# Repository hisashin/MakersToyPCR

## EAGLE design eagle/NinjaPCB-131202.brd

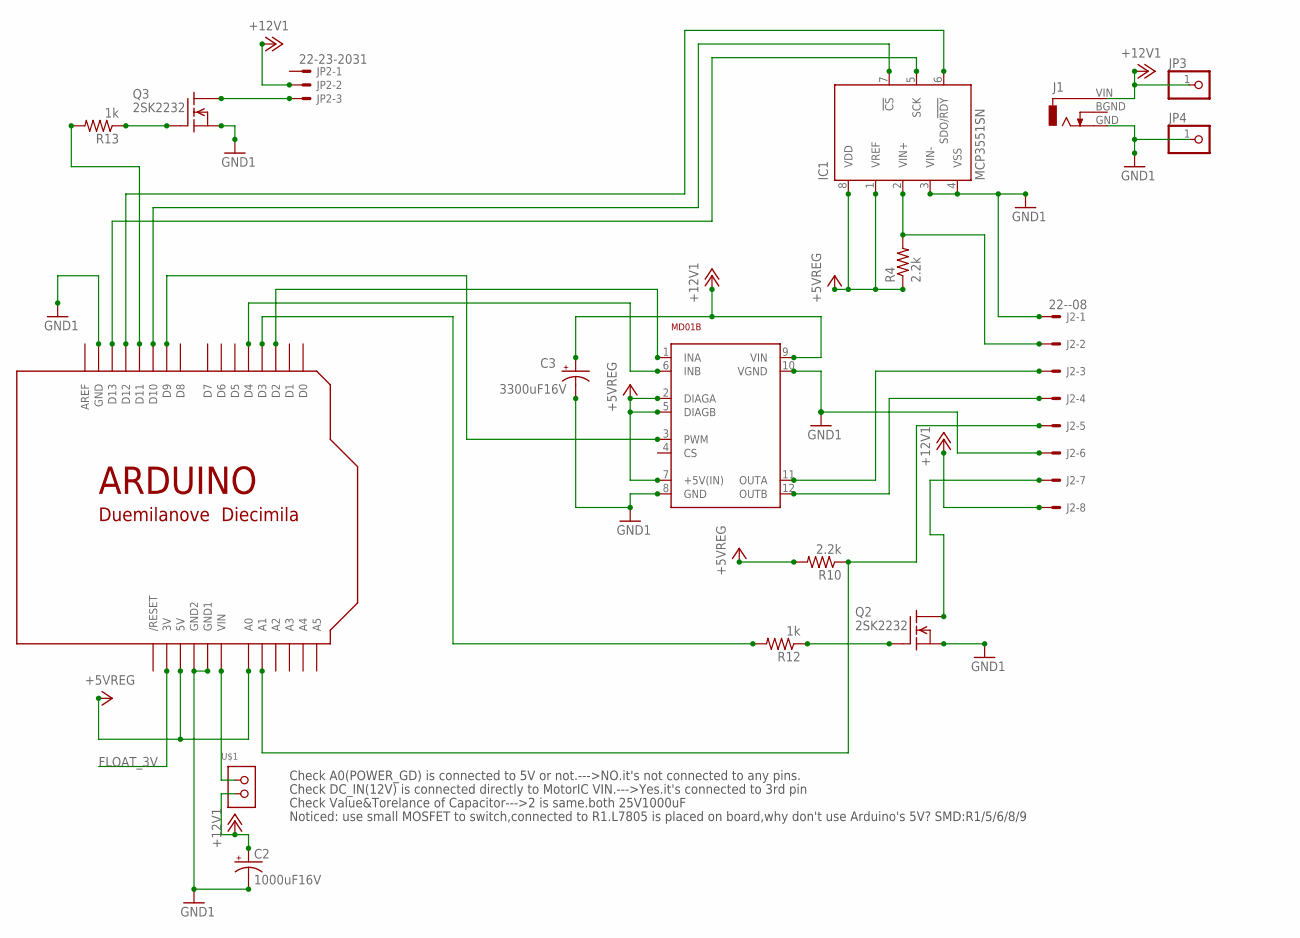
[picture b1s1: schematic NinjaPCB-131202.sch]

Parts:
C2: 1000uF16V; E5-8,5
C3: 3300uF16V; E5-13
IC1: MCP3551SN; SO-08
J1: DCJ0303
J2: 22--08; POLOLU-8-VERTICAL
JP2: 22-23-2031
JP3, JP4: PINHD-1X1; 1X01
MD01B: VNH3SP30+4PINN; VNH3SP30+4PIN_NOHOLES
Q2, Q3: 2SK2232; TO202
R4, R10: 2.2k; 0207/10
R12, R13: 1k; 0207/10
U$1: 1X02; 1X02_1.1_UNSIGNED
U$3: Arduino UNO; ARDUINO-NOSILK

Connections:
+5VREG: IC1.1 (VREF), IC1.8 (VDD), MD01B.2 (DIAGA), MD01B.5 (DIAGB), MD01B.7 (+5V(IN)), R4.1, R10.2, U$3.5V, U$3.A0
+12V1: C2.+, C3.+, J1.VIN, J2.8, JP2.2, JP3.1, MD01B.9 (VIN), U$1.2
D13: IC1.5 (SCK), U$3.D13
FLOAT_3V: U$3.3V
GND1: C2.-, C3.-, IC1.3 (VIN-), IC1.4 (VSS), J1.GND, J2.1, J2.6, JP4.1, MD01B.8 (GND), MD01B.10 (VGND), Q2.1 (S), Q3.1 (S), U$3.GND, U$3.GND1, U$3.GND2
unnamed: JP2.3, Q3.2 (D)
unnamed: Q3.3 (G), R13.1
unnamed: R13.2, U$3.D11
unnamed: U$1.1, U$3.VIN
unnamed: R12.2, U$3.D3
unnamed: J2.7, Q2.2 (D)
unnamed: IC1.2 (VIN+), J2.2, R4.2
unnamed: IC1.6 (SDO/!RDY), U$3.D12
unnamed: IC1.7 (!CS), U$3.D10
unnamed: J2.5, R10.1, U$3.A1
OUTA: J2.3, MD01B.11 (OUTA)
OUTB: J2.4, MD01B.12 (OUTB)
S$1: MD01B.1 (INA), U$3.D2
S$2: MD01B.3 (PWM), U$3.D9
S$3: MD01B.6 (INB), U$3.D4
T1: Q2.3 (G), R12.1

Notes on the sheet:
Check A0(POWER_GD) is connected to 5V or not.--->NO.it's not connected to any pins.
Check DC_IN(12V) is connected directly to MotorIC VIN.--->Yes.it's connected to 3rd pin
Check Value&Torelance of Capacitor--->2 is same.both 25V1000uF
Noticed: use small MOSFET to switch,connected to R1.L7805 is placed on board,why don't use Arduino's 5V? SMD:R1/5/6/8/9

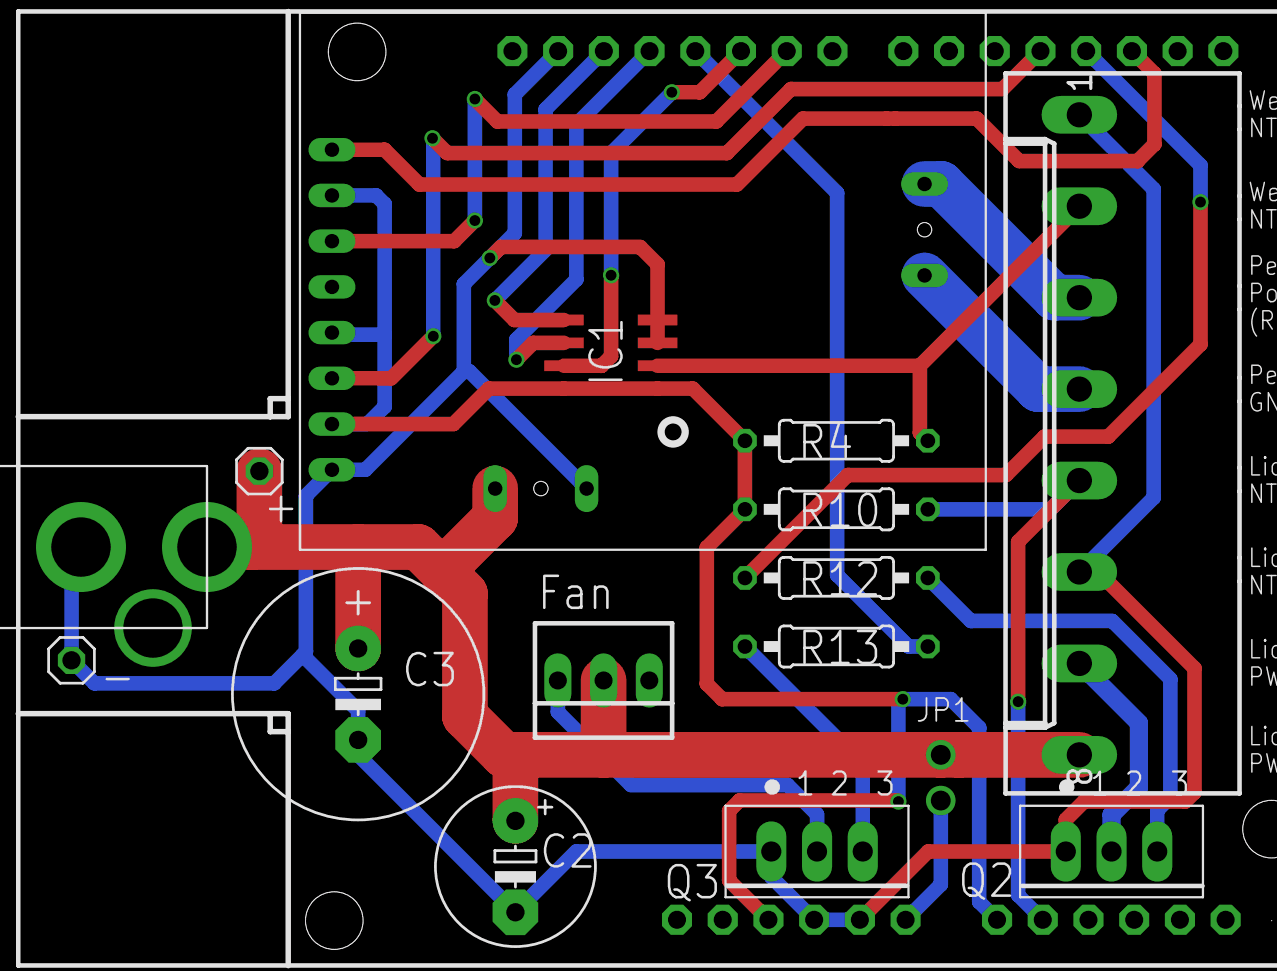
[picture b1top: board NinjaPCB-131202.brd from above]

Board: 2 copper layers, 17 parts (0 on the bottom side), 20 nets.

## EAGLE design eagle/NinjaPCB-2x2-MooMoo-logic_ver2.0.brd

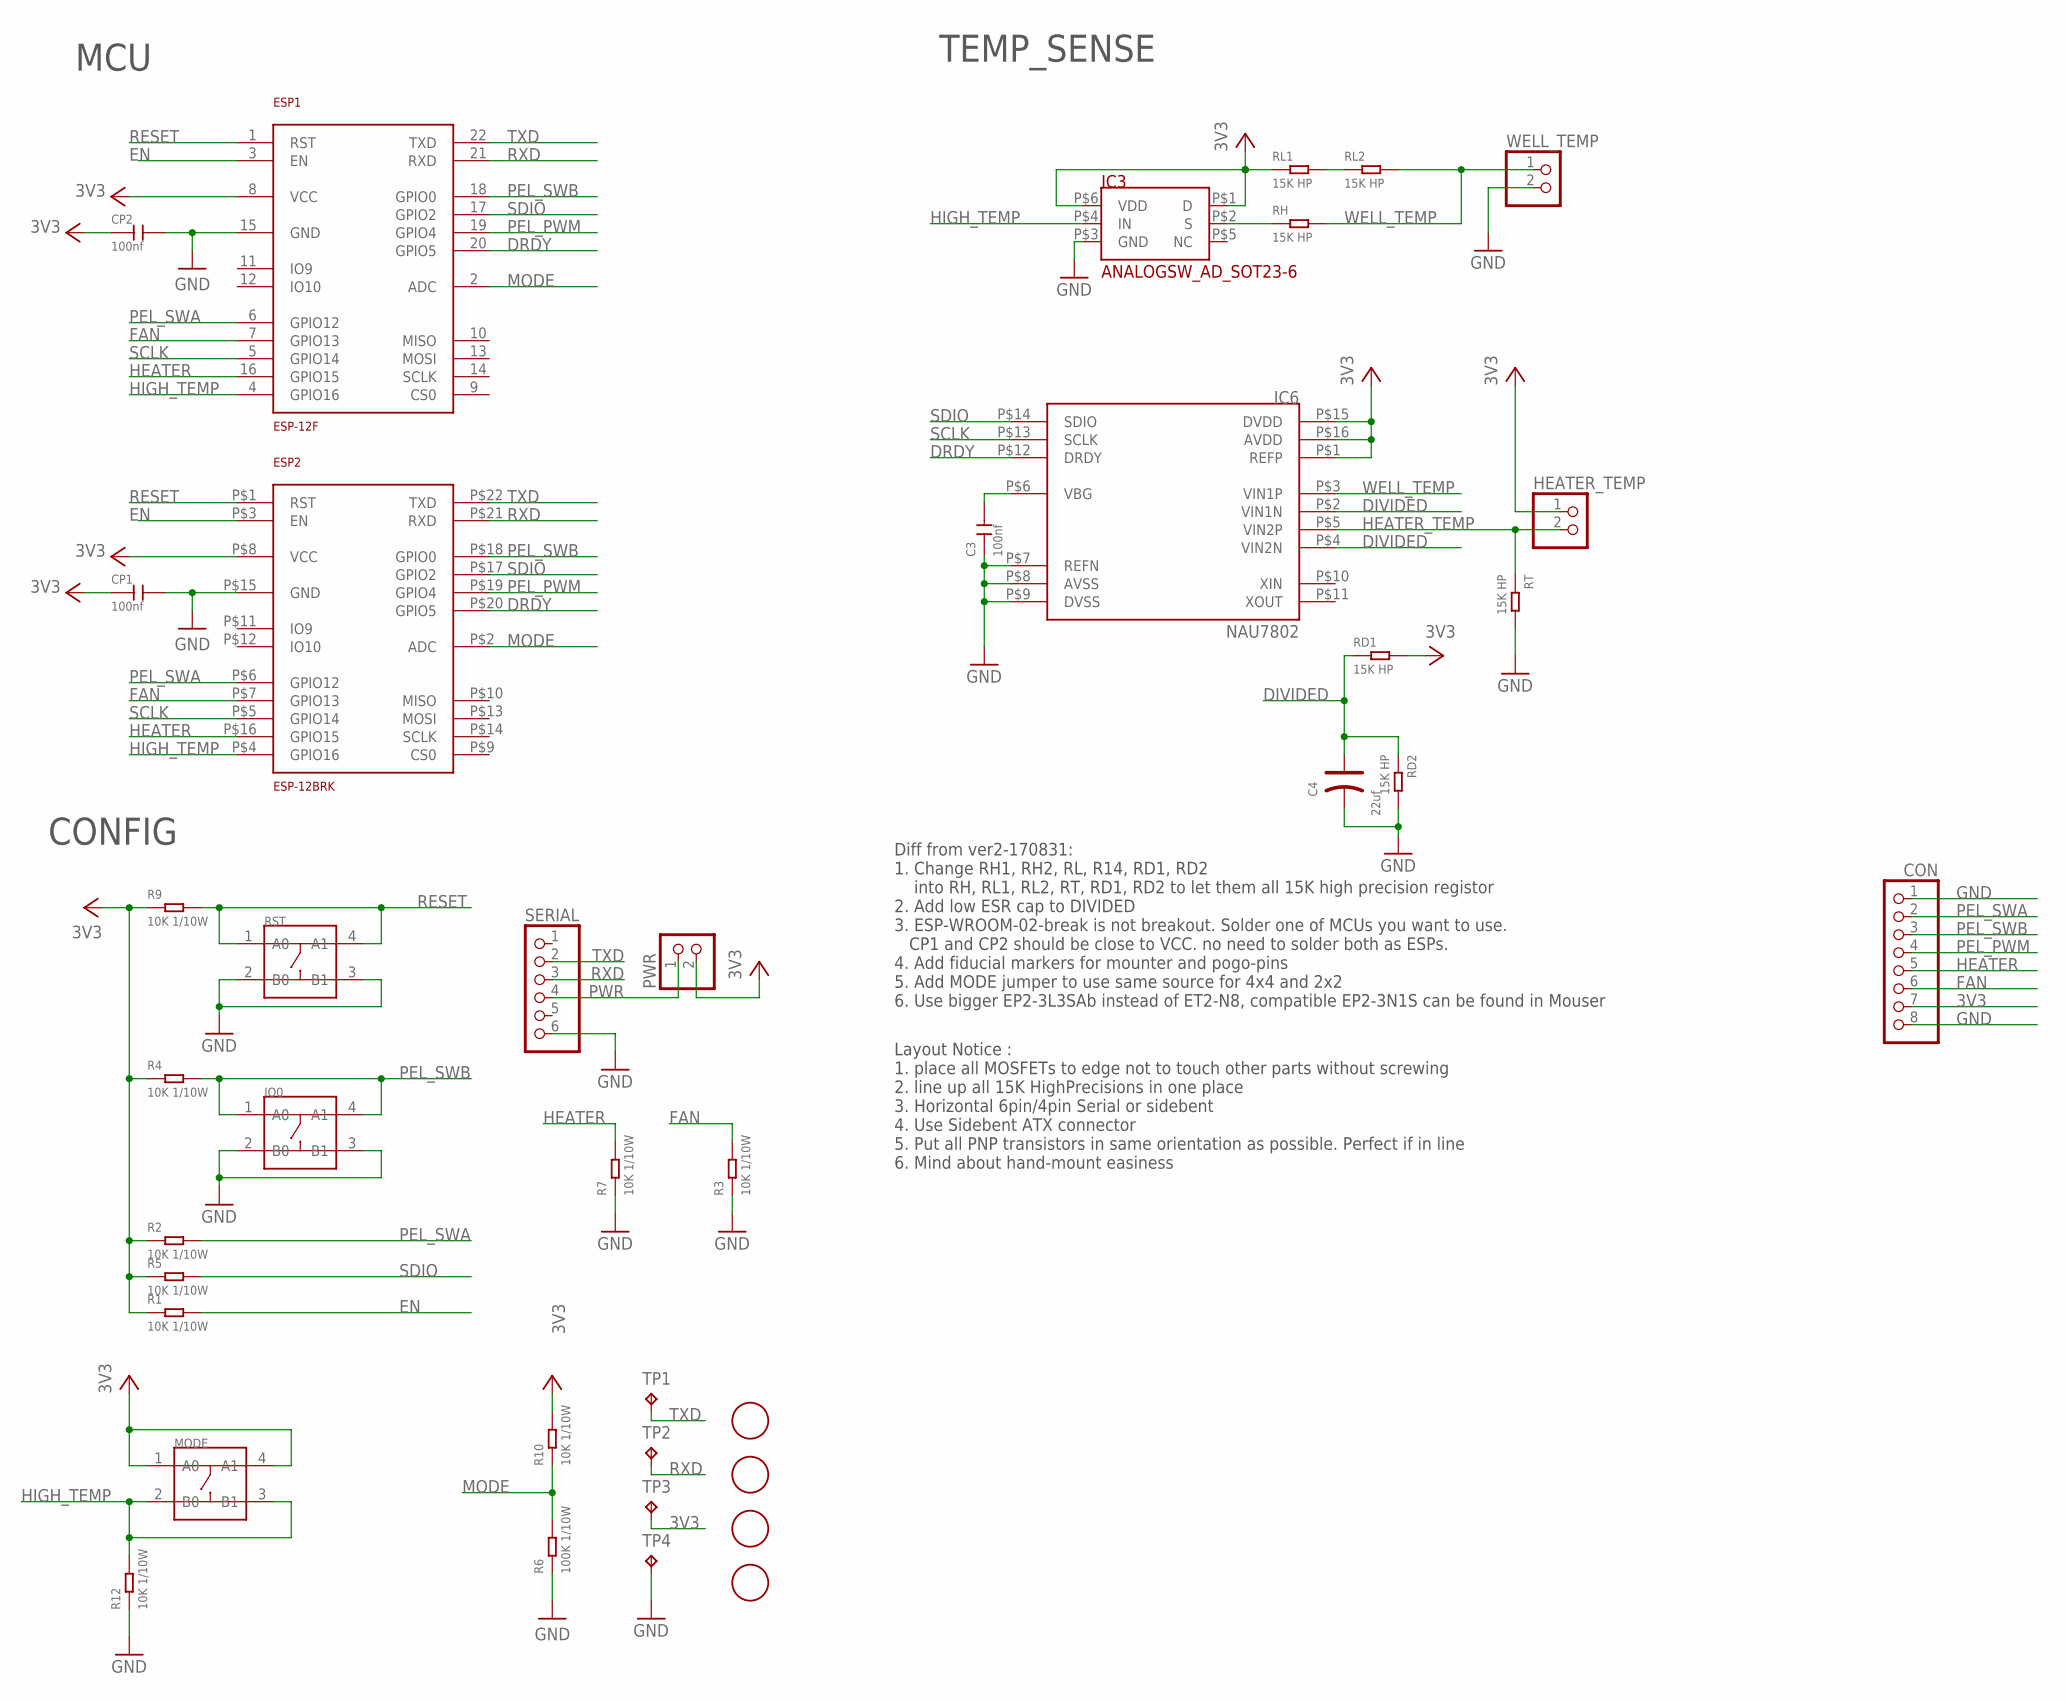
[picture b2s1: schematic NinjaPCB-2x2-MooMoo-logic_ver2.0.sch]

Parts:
C3: 100nf; C0603
C4: 22uf; AVX-B
CON: PINHD-1X8; 1X08
CP1, CP2: 100nf; C0603
ESP1: ESP-12F
ESP2: ESP-12BRK; ESP-12-BREAK
HEATER_TEMP: PINHD-1X2; 1X02
IC3: ANALOGSW_AD_SOT23-6; SOT-23-6
IC6: NAU7802; SOP-16
IO0: DIP-SWITCH-TACTILE-SPST-NO/TS-1109(4P-D6.0MM)'TS-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; SW4-6.0X6.0X5.0MM
MODE: DIP-SWITCH-TACTILE-SPST-NO/TS-1109(4P-D6.0MM)'TS-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; SW4-6.0X6.0X5.0MM
PWR: PINHD-1X2; 1X02
R1, R2, R3, R4, R5, R7, R9, R10, R12: 10K 1/10W; R0603
R6: 100K 1/10W; R0603
RD1, RD2: 15K HP; R0603
RH: 15K HP; R0603
RL1, RL2: 15K HP; R0603
RST: DIP-SWITCH-TACTILE-SPST-NO/TS-1109(4P-D6.0MM)'TS-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; SW4-6.0X6.0X5.0MM
RT: 15K HP; R0603
SERIAL: PINHD-1X6; 1X06
TP1, TP2, TP3, TP4: TPTP20R; TP20R
U$3, U$4, U$5, U$6: FIDUCIAL; FIDUCIAL_1MM
WELL_TEMP: PINHD-1X2; 1X02

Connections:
3V3: CP1.1, CP2.1, ESP1.8 (VCC), ESP2.P$8 (VCC), HEATER_TEMP.1, IC3.P$1 (D), IC3.P$6 (VDD), IC6.P$1 (REFP), IC6.P$15 (DVDD), IC6.P$16 (AVDD), MODE.1 (A0), MODE.4 (A1), PWR.2, R1.1, R2.1, R4.1, R5.1, R9.1, R10.2, RD1.2, RL1.1, TP3.TP
DIVIDED: C4.+, IC6.P$2 (VIN1N), IC6.P$4 (VIN2N), RD1.1, RD2.1
DRDY: ESP1.20 (GPIO5), ESP2.P$20 (GPIO5), IC6.P$12 (DRDY)
EN: ESP1.3 (EN), ESP2.P$3 (EN), R1.2
FAN: ESP1.7 (GPIO13), ESP2.P$7 (GPIO13), R3.2
GND: C3.1, C4.-, CON.1, CP1.2, CP2.2, ESP1.15 (GND), ESP2.P$15 (GND), IC3.P$3 (GND), IC6.P$7 (REFN), IC6.P$8 (AVSS), IC6.P$9 (DVSS), IO0.2 (B0), IO0.3 (B1), R3.1, R6.1, R7.1, R12.1, RD2.2, RST.2 (B0), RST.3 (B1), RT.2, SERIAL.6, TP4.TP, WELL_TEMP.2
HEATER: ESP1.16 (GPIO15), ESP2.P$16 (GPIO15), R7.2
HEATER_TEMP: HEATER_TEMP.2, IC6.P$5 (VIN2P), RT.1
HIGH_TEMP: ESP1.4 (GPIO16), ESP2.P$4 (GPIO16), IC3.P$4 (IN), MODE.2 (B0), MODE.3 (B1), R12.2
MODE: ESP1.2 (ADC), ESP2.P$2 (ADC), R6.2, R10.1
unnamed: RL1.2, RL2.1
unnamed: IC3.P$2 (S), RH.1
unnamed: C3.2, IC6.P$6 (VBG)
PEL_PWM: ESP1.19 (GPIO4), ESP2.P$19 (GPIO4)
PEL_SWA: ESP1.6 (GPIO12), ESP2.P$6 (GPIO12), R2.2
PEL_SWB: ESP1.18 (GPIO0), ESP2.P$18 (GPIO0), IO0.1 (A0), IO0.4 (A1), R4.2
PWR: PWR.1, SERIAL.4
RESET: ESP1.1 (RST), ESP2.P$1 (RST), R9.2, RST.1 (A0), RST.4 (A1)
RXD: ESP1.21 (RXD), ESP2.P$21 (RXD), SERIAL.3, TP2.TP
SCLK: ESP1.5 (GPIO14), ESP2.P$5 (GPIO14), IC6.P$13 (SCLK)
SDIO: ESP1.17 (GPIO2), ESP2.P$17 (GPIO2), IC6.P$14 (SDIO), R5.2
TXD: ESP1.22 (TXD), ESP2.P$22 (TXD), SERIAL.2, TP1.TP
WELL_TEMP: IC6.P$3 (VIN1P), RH.2, RL2.2, WELL_TEMP.1

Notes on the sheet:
TEMP_SENSE
MCU
Diff from ver2-170831: 1. Change RH1, RH2, RL, R14, RD1, RD2 into RH, RL1, RL2, RT, RD1, RD2 to let them all 15K high precision registor 2. Add low ESR cap to DIVIDED 3. ESP-WROOM-02-break is not breakout. Solder one of MCUs you want to use. CP1 and CP2 should be close to VCC. no need to solder bot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
CONFIG
Layout Notice : 1. place all MOSFETs to edge not to touch other parts without screwing 2. line up all 15K HighPrecisions in one place 3. Horizontal 6pin/4pin Serial or sidebent 4. Use Sidebent ATX connector 5. Put all PNP transistors in same orientation as possible. Perfect if in line 6. Mind about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

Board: 2 copper layers, 40 parts (0 on the bottom side), 23 nets, no tracks yet.
